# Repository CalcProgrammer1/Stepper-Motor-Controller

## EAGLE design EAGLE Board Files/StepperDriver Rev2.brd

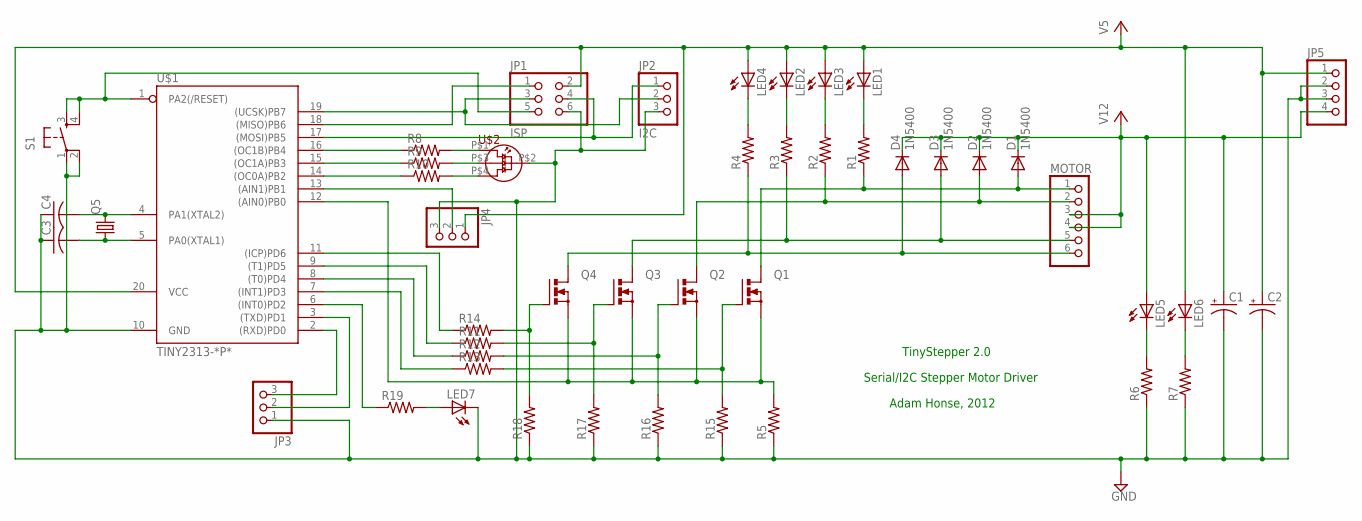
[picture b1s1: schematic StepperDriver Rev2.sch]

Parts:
C1, C2: CPOL-USE7.5-16; E7,5-16
C3, C4: C-US025-024X044; C025-024X044
D1, D2, D3, D4: 1N5400; DO201-15
JP1: ISP; 2X03
JP2: I2C; 1X03
JP3, JP4: PINHD-1X3; 1X03
JP5: PINHD-1X4; 1X04
LED1, LED2, LED3, LED4, LED5, LED6, LED7: LED5MM
MOTOR: PINHD-1X6; 1X06
Q1, Q2, Q3, Q4: PMOSFET_NTO220BV; TO220BV
Q5: CRYSTALHC49U70; HC49U70
R1, R2, R3, R4, R6, R7, R8, R9, R10, R11, R12, R13, R14, R15, R16, R17, R18, R19: R-US_0204/7; 0204/7
R5: R-US_0617/22; 0617/22
S1: TAC_SWITCHPTH; TACTILE-PTH
U$1: TINY2313-*P*; DIL20
U$2: 5MMRGBLED; LED5MMRGB

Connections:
GND: C1.-, C2.-, C3.1, C4.1, JP1.6, JP2.3, JP3.1, JP4.3, JP5.2, JP5.3, LED7.K (C), R5.1, R6.1, R7.1, R15.1, R16.1, R17.1, R18.1, S1.1, S1.2, U$1.10 (GND), U$2.P$2 (CATHODE)
unnamed: LED4.K (C), R4.2
unnamed: D2.A, MOTOR.2, Q2.D, R2.1
unnamed: D1.A, MOTOR.1, Q1.D, R1.1
unnamed: D3.A, MOTOR.5, Q3.D, R3.1
unnamed: D4.A, MOTOR.6, Q4.D, R4.1
unnamed: LED2.K (C), R3.2
unnamed: LED3.K (C), R2.2
unnamed: LED1.K (C), R1.2
unnamed: JP3.3, U$1.2 ((RXD)PD0)
unnamed: JP3.2, U$1.3 ((TXD)PD1)
unnamed: Q1.S, Q2.S, Q3.S, Q4.S, R5.2, U$1.12 ((AIN0)PB0)
unnamed: R13.1, U$1.7 ((INT1)PD3)
unnamed: R12.1, U$1.8 ((T0)PD4)
unnamed: R11.1, U$1.9 ((T1)PD5)
unnamed: Q1.G, R13.2, R15.2
unnamed: JP1.1, U$1.18 ((MISO)PB6)
unnamed: JP1.5, S1.3, S1.4, U$1.1 (PA2(/RESET))
unnamed: R10.2, U$2.P$4 (BLUE)
unnamed: JP1.3, JP2.2, U$1.19 ((UCSK)PB7)
unnamed: LED5.K (C), R6.2
unnamed: JP1.4, JP2.1, U$1.17 ((MOSI)PB5)
unnamed: LED6.K (C), R7.2
unnamed: R9.2, U$2.P$3 (GREEN)
unnamed: R8.2, U$2.P$1 (RED)
unnamed: R10.1, U$1.14 ((OC0A)PB2)
unnamed: R9.1, U$1.15 ((OC1A)PB3)
unnamed: R8.1, U$1.16 ((OC1B)PB4)
unnamed: Q2.G, R12.2, R16.2
unnamed: Q3.G, R11.2, R17.2
unnamed: Q4.G, R14.2, R18.2
unnamed: R14.1, U$1.11 ((ICP)PD6)
unnamed: C3.2, Q5.1, U$1.5 (PA0(XTAL1))
unnamed: LED7.A, R19.2
unnamed: R19.1, U$1.6 ((INT0)PD2)
unnamed: C4.2, Q5.2, U$1.4 (PA1(XTAL2))
unnamed: JP4.2, U$1.13 ((AIN1)PB1)
V5: C2.+, JP1.2, JP4.1, JP5.1, LED1.A, LED2.A, LED3.A, LED4.A, LED6.A, U$1.20 (VCC)
V12: C1.+, D1.C, D2.C, D3.C, D4.C, JP5.4, LED5.A, MOTOR.3, MOTOR.4

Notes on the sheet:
TinyStepper 2.0
Serial/I2C Stepper Motor Driver
Adam Honse, 2012

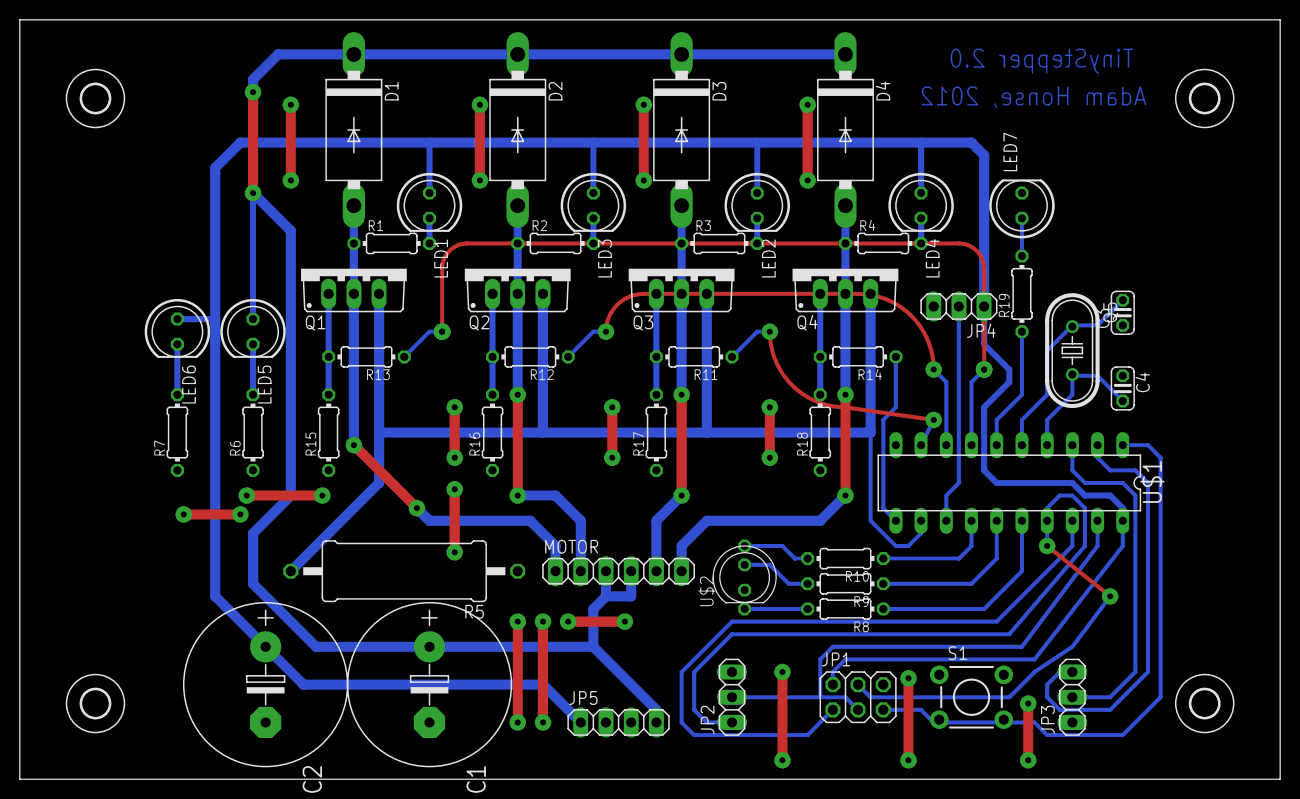
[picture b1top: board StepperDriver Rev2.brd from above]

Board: 2 copper layers, 127.0 x 76.5 mm, 52 parts (0 on the bottom side), 39 nets.

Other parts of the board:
U$3, U$4, U$5, U$6: 2,8

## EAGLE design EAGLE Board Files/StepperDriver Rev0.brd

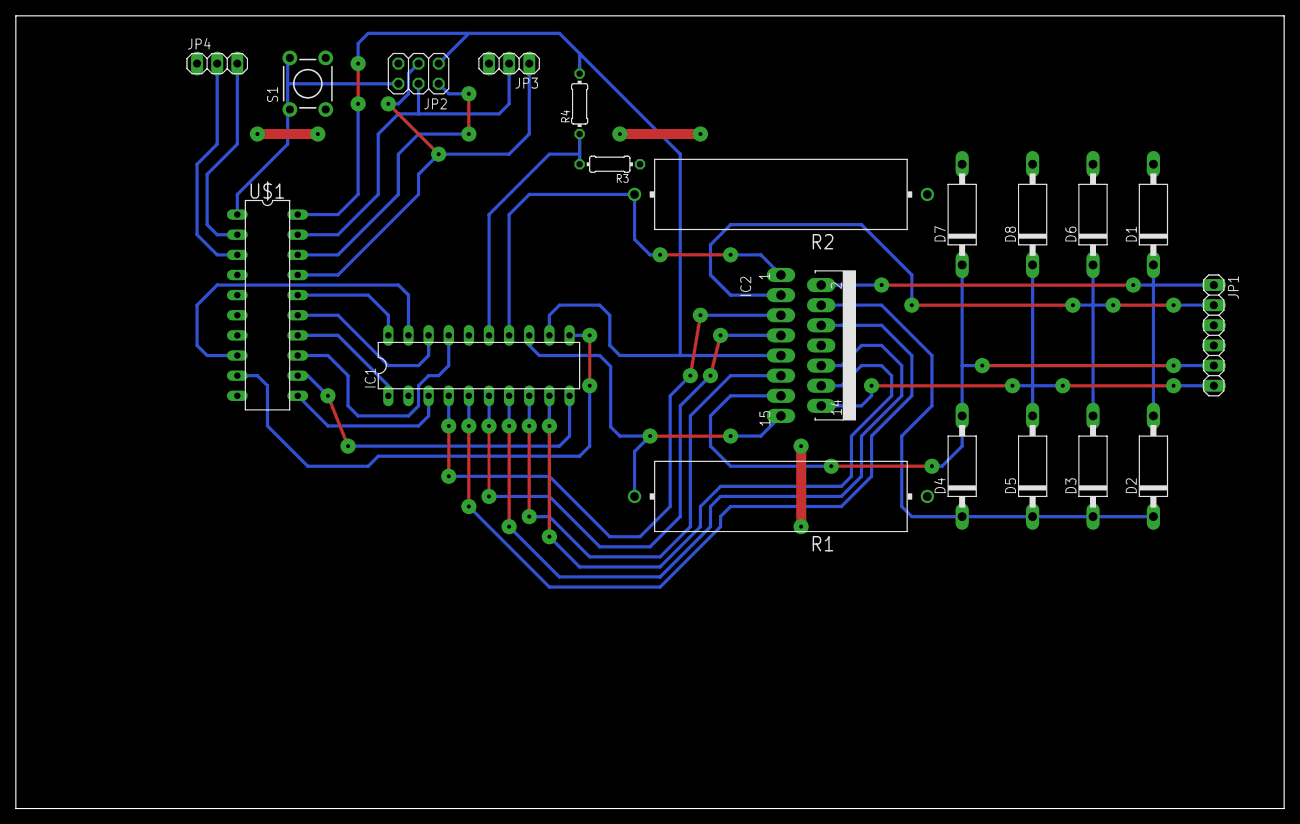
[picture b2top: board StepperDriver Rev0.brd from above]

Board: 2 copper layers, 160.0 x 100.0 mm, 20 parts (0 on the bottom side), 30 nets.

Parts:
D1, D2, D3, D4, D5, D6, D7, D8: 1N5060GP; DO15-12
IC1: L297; DIL20
IC2: L298; MULTIWATT-15
JP1: MOTOR; 1X06
JP2: ISP; 2X03
JP3: I2C; 1X03
JP4: SERIAL; 1X03
R1, R2: 0.47; HPS932
R3: 1K; 0204/7
R4: 10K; 0204/7
S1: TACTILE-PTH
U$1: TINY2313-*P*; DIL20

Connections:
GND: D1.A, D6.A, D7.A, D8.A, IC1.2, IC2.8, JP2.5, JP3.3, JP4.1, R1.1, R2.1, R3.1, S1.3, S1.4, U$1.10
unnamed: IC1.10, U$1.12
unnamed: D2.C, D3.C, D4.C, D5.C, IC2.4
unnamed: IC1.14, IC2.1, R2.2
unnamed: IC1.18, U$1.15
unnamed: IC1.17, U$1.13
unnamed: IC1.20, U$1.16
unnamed: IC1.13, IC2.15, R1.2
unnamed: IC1.1, U$1.14
unnamed: IC1.19, U$1.8
unnamed: IC1.12, IC2.9, JP2.1, R4.2, U$1.20
unnamed: D4.A, D7.C, IC2.13, JP1.5
unnamed: IC1.4, IC2.5
unnamed: JP4.2, U$1.3
unnamed: IC1.15, R3.2, R4.1
unnamed: JP4.3, U$1.2
unnamed: JP2.3, JP3.1, U$1.17
unnamed: JP2.2, U$1.18
unnamed: JP2.4, JP3.2, U$1.19
unnamed: D1.C, D2.A, IC2.2, JP1.1
unnamed: IC1.5, IC2.6
unnamed: IC1.3, U$1.11
unnamed: JP2.6, S1.1, S1.2, U$1.1
unnamed: IC1.6, IC2.7
unnamed: IC1.7, IC2.10
unnamed: D5.A, D8.C, IC2.14, JP1.6
unnamed: IC1.8, IC2.11
unnamed: IC1.9, IC2.12
unnamed: D3.A, D6.C, IC2.3, JP1.2
unnamed: IC1.11, U$1.9

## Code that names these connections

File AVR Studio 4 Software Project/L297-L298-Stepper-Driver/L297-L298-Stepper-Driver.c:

/*-------------------------------------------------------------*\
|  L297 Stepper Motor Controller with Serial and I2C Interface	|
|  Based on ATTiny2313 microcontroller, this motor controller	|
|  can drive stepper motors using the ST L297/298 chipset		|
|																|
|  Adam Honse (amhb59@mail.mst.edu, calcprogrammer1@gmail.com)	|
|  3/16/2012, Designed for Senior Design Project				|
\*-------------------------------------------------------------*/

#include <avr/io.h>
#include <avr/interrupt.h>
#include <util/delay.h>
#include "serial.h"
#include "usi_i2c_master.h"

//L297 Pins on Port B
#define L297_PORTB_DDR			0b00011111
#define L297_PIN_HF				PB0
#define L297_PIN_CW_CCW			PB1
#define L297_PIN_CLOCK			PB2
#define L297_PIN_SYNC			PB3
#define L297_PIN_ENABLE			PB4

//L297 Pins on Port D
#define L297_PORTD_DDR			0b01100000
#define L297_PIN_HOME			PD2
#define L297_PIN_CNTL			PD5
#define L297_PIN_RESET			PD6

//Set up the timer overflow to generate a clock for the L297's SYNC line
void setup_l297_clock()
{
   DDRB = L297_PORTB_DDR;
   DDRD = L297_PORTD_DDR;

   OCR1A = 0;
   TCCR1A  = ((1 << COM1A1) | (1 << WGM10) | (1 << WGM11));
   TCCR1B  = ((1 << CS10) | (0 << CS11) | (1 << CS12) | (0 << WGM12));
   TIMSK  = (0<<OCIE1B);

   OCR1A = 255;
}


int main()
{
	//Initialize serial interface to 38400 baud
	serial_init(12);

	//Start SYNC clock for L297
	setup_l297_clock();

	//Start USI I2C Interface
	usi_i2c_master_initialize();

	//Enable L297
	PORTB |= (1 << L297_PIN_ENABLE);

	while(1)
	{
		_delay_ms(1000);
		usi_i2c_master_stop();
	}
}

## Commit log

2012-04-13 added board files
2012-07-31 Updated USI I2C drivers for master and slave, implemented registers interface

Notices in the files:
parts and their libraries:
SparkFun-Electromechanical: Licensing: CC v3.0 Share-Alike You are welcome to use this library for commercial purposes.
